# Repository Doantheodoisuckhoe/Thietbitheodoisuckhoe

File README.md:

# Thiết bị đeo tay giám sát sức khỏe người cao tuổi

Đồ án tốt nghiệp ngành Điện tử – Viễn thông.

Thiết bị đeo tay theo dõi nhịp tim, SpO2, nhiệt độ da, ECG 1 chuyển đạo và ước lượng huyết áp (PAT),
phát hiện té ngã, gửi cảnh báo tự động đến người thân qua app, web và SMS.

> Nguyên mẫu nghiên cứu, **không phải thiết bị y tế**, không dùng để chẩn đoán.

## Kiến trúc

```
Đồng hồ (XIAO nRF52840 Sense + module MAX30102 + AD8232 + MAX30205)
   │ BLE
   ▼
App Android (Flutter) ──Internet──► Server (FastAPI + PostgreSQL)
                                        │ khi vượt ngưỡng
                                        ▼
                         Người nhà, bác sĩ: push, SMS, web dashboard
```

## Cấu trúc thư mục

| Thư mục | Nội dung | Phụ trách |
|---|---|---|
| `firmware/` | Code Arduino/C cho XIAO nRF52840: đọc cảm biến, xử lý tín hiệu, BLE | SV1 |
| `algorithm/` | Thuật toán viết và kiểm thử bằng Python (nhịp tim, SpO2, Pan-Tompkins, PAT, té ngã) | SV2 |
| `app/` | App Flutter cho người đeo và người nhà; web dashboard (Flutter Web) | SV2 |
| `server/` | Backend FastAPI, cơ sở dữ liệu, bộ xử lý cảnh báo, gửi push/SMS | SV2 |
| `hardware/pcb_module/` | KiCad bản ghép module đang làm: sơ đồ, PCB 2 lớp, Gerber, BOM | SV1 |
| `hardware/pcb/` | KiCad bản chip rời 40 × 40 mm (lưu trữ, hướng phát triển) | SV1 |
| `hardware/enclosure/` | File thiết kế vỏ (Fusion 360, STL) | SV1 |
| `data/` | Dữ liệu đo thô (CSV) và kết quả kiểm chứng | Chung |
| `docs/` | Tài liệu, hình ảnh cho báo cáo | Chung |

## Phần cứng

| Khối | Linh kiện |
|---|---|
| Vi điều khiển + BLE + IMU | Seeed XIAO nRF52840 Sense |
| PPG (nhịp tim, SpO2) | Module MAX30102 (bản chip rời MAX30101 để hướng phát triển) |
| ECG 1 chuyển đạo | Module AD8232 |
| Nhiệt độ da | Module MAX30205 (CJMCU-30205) |
| Hiển thị, cảnh báo | Màn hình tròn 1,28" GC9A01, motor rung, nút SOS |
| Nguồn | Pin LiPo 603040 (có mạch bảo vệ), sạc qua chân pogo nam châm |

## Cài đặt môi trường

**Firmware (Arduino IDE)**
1. File → Preferences → Additional boards manager URLs:
   `https://files.seeedstudio.com/arduino/package_seeeduino_boards_index.json`
2. Boards Manager → cài **Seeed nRF52 Boards** (1.1.13) → chọn board **Seeed XIAO nRF52840 Sense**.
3. Library Manager → cài: SparkFun MAX3010x Pulse and Proximity Sensor Library, OneWire,
   DallasTemperature, Adafruit GC9A01A (chọn *Install all* để cài kèm Adafruit GFX, BusIO), Seeed Arduino LSM6DS3.
4. Mở `firmware/kiem_tra_thu_vien` và bấm Verify để kiểm tra. Phiên bản đã kiểm chứng và các lỗi
   thường gặp: [`firmware/README.md`](firmware/README.md).

**Vỏ thiết bị:** Onshape (gói Education, đăng ký bằng email sinh viên), xuất STL vào `hardware/enclosure/`.

**Thuật toán (Python 3.10+)**
```
pip install numpy scipy matplotlib wfdb pandas
```

## Mốc tiến độ

| Mốc | Hạn | Tiêu chí |
|---|---|---|
| M1 | 11/10/2026 | Đề cương được duyệt, linh kiện đã đặt |
| M2 | 01/11/2026 | Breadboard đo đủ chỉ số qua BLE; đã đặt mạch JLCPCB |
| M3 | 22/11/2026 | Thiết bị đeo tay chạy đầu-cuối ổn định 24 giờ |
| M4 | 06/12/2026 | Bản thảo báo cáo đầy đủ gửi GVHD |

## Tài liệu và công cụ của nhóm

| Ở đâu | Có gì |
|---|---|
| [`docs/nhat-ky.md`](docs/nhat-ky.md) | Nhật ký thực hiện và các quyết định theo ngày |
| [`docs/mua-sam/`](docs/mua-sam/) | Danh sách mua linh kiện, máy đo đối chứng, ngân sách |
| Trello: bảng *Đồ án – Thiết bị đeo tay giám sát sức khỏe* | Việc từng tuần, mốc; báo cáo tiến độ tự động tối Chủ Nhật |
| Google Drive: thư mục *Đồ án tốt nghiệp – Thiết bị đeo tay giám sát sức khỏe* | Datasheet, dữ liệu đo dài, báo cáo, ảnh/video, file phát hành mạch và vỏ, giấy tờ |

## Làm việc với Git trên máy

Thư mục làm việc trên máy SV1: `C:\DoAnTotNghiep` (bản clone của repo này).

1. Trước khi làm: mở Git Bash trong thư mục đó, chạy `git pull` để lấy thay đổi mới nhất.
2. Sau khi làm xong một việc nhỏ:
   ```
   git add .
   git commit -m "firmware: mô tả ngắn việc vừa làm"
   git push
   ```
3. Lần đầu `git push`, Windows sẽ mở cửa sổ đăng nhập GitHub — đăng nhập một lần là xong.

## Quy ước làm việc

- Mỗi người làm trên nhánh riêng (`sv1/...`, `sv2/...`), gộp vào `main` khi chạy được.
- Commit nhỏ, mô tả rõ bằng tiếng Việt, ví dụ: `firmware: đọc FIFO MAX30102 ở 100 Hz`.
- Không đẩy file lớn hơn 50 MB; dữ liệu đo dài lưu trên Drive, chỉ để mẫu nhỏ trong `data/`.

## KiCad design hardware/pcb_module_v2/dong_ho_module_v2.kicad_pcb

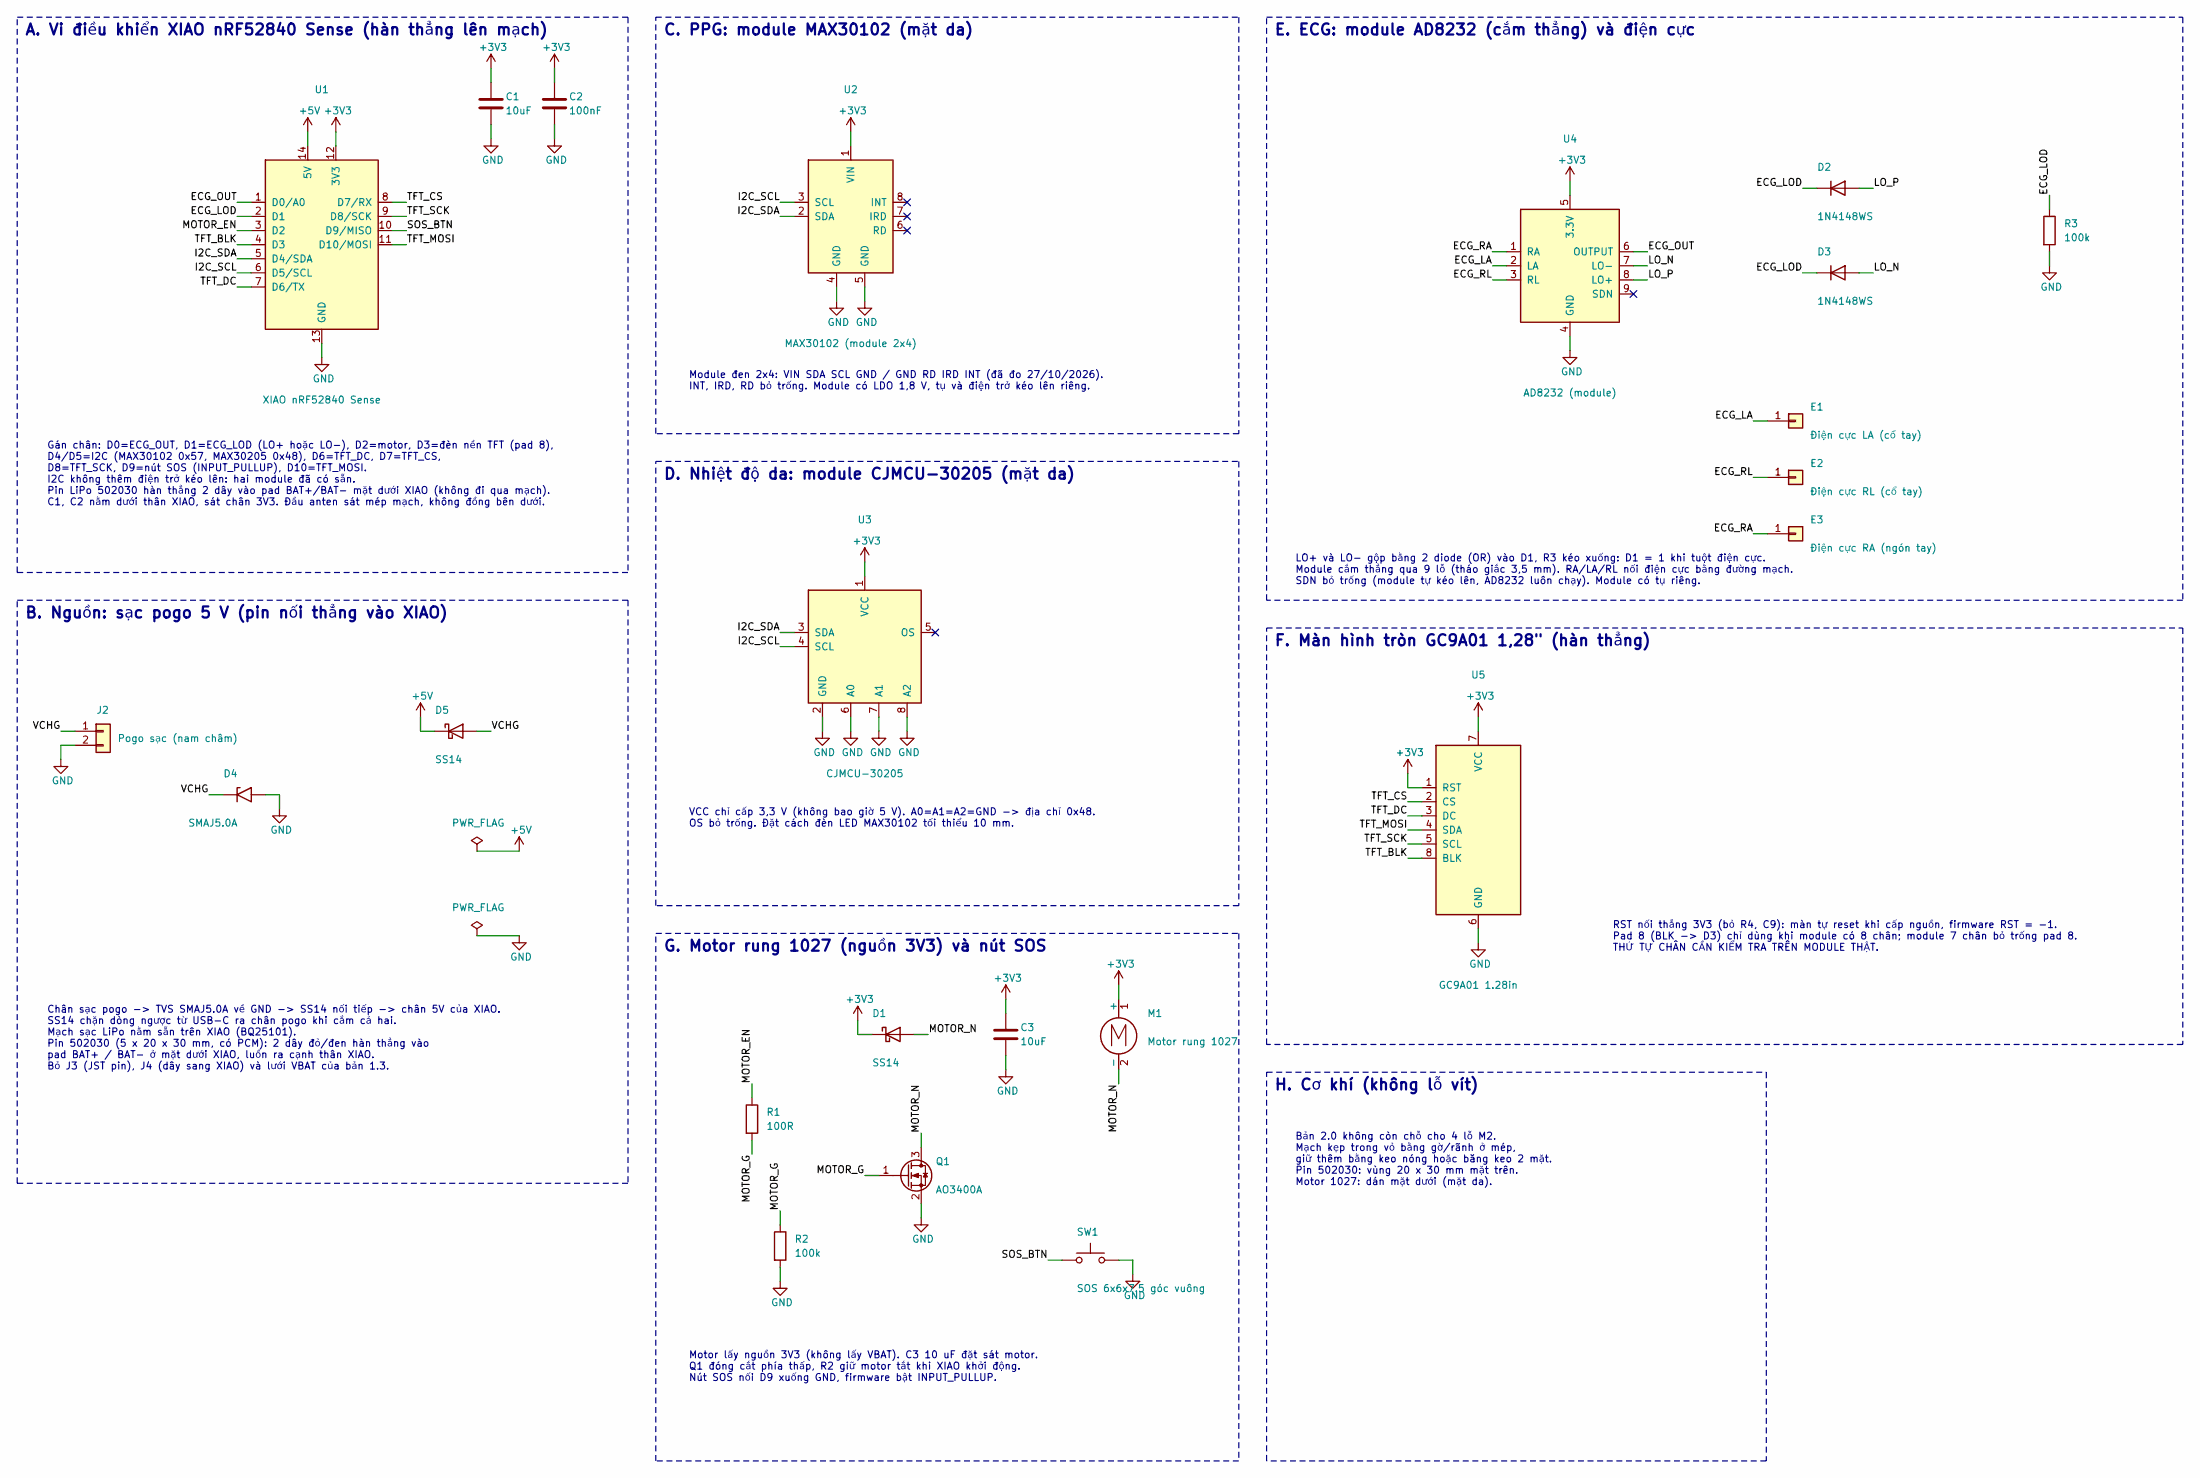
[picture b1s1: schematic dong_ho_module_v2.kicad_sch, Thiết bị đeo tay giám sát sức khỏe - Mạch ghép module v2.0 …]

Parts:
C1, C3: 10uF; C_0805_2012Metric
C2: 100nF; C_0805_2012Metric
D1, D5: SS14; D_SMA
D2, D3: 1N4148WS; D_SOD-323
D4: SMAJ5.0A; D_SMA
E1: Điện cực LA (cổ tay); DienCuc_ECG_9x16mm
E2: Điện cực RL (cổ tay); DienCuc_ECG_9x16mm
E3: Điện cực RA (ngón tay); DienCuc_RA_8x9.6mm
J2: Pogo sạc (nam châm); Pogo_2pad_P2.54_TAM
M1: Motor rung 1027; Motor_1027_2pad_P4.0_TAM
Q1: AO3400A; SOT-23
R1: 100R; R_0805_2012Metric
R2, R3: 100k; R_0805_2012Metric
SW1: SOS 6x6x7.5 góc vuông; SW_SOS_6x6_GocVuong_TAM
U1: XIAO nRF52840 Sense; XIAO_nRF52840_DeCam_2x7_P2.54_15.24mm
U2: MAX30102 (module 2x4); Module_MAX30102_2x4
U3: CJMCU-30205; Module_CJMCU-30205_1x8
U4: AD8232 (module); Module_AD8232_9chan
U5: GC9A01 1.28in; Display_GC9A01_8chan

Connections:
+3V3: C1.1, C2.1, C3.1, D1.1 (K), M1.1 (+), U1.12 (3V3), U2.1 (VIN), U3.1 (VCC), U4.5 (3.3V), U5.1 (RST), U5.7 (VCC)
+5V: D5.1 (K), U1.14 (5V)
/ECG_LA: E1.1, U4.2 (LA)
/ECG_LOD: D2.1 (K), D3.1 (K), R3.1, U1.2 (D1)
/ECG_OUT: U1.1 (D0/A0), U4.6 (OUTPUT)
/ECG_RA: E3.1, U4.1 (RA)
/ECG_RL: E2.1, U4.3 (RL)
/I2C_SCL: U1.6 (D5/SCL), U2.3 (SCL), U3.4 (SCL)
/I2C_SDA: U1.5 (D4/SDA), U2.2 (SDA), U3.3 (SDA)
/LO_N: D3.2 (A), U4.7 (LO-)
/LO_P: D2.2 (A), U4.8 (LO+)
/MOTOR_EN: R1.1, U1.3 (D2)
/MOTOR_G: Q1.1 (G), R1.2, R2.1
/MOTOR_N: D1.2 (A), M1.2 (-), Q1.3 (D)
/SOS_BTN: SW1.1, U1.10 (D9/MISO)
/TFT_BLK: U1.4 (D3), U5.8 (BLK)
/TFT_CS: U1.8 (D7/RX), U5.2 (CS)
/TFT_DC: U1.7 (D6/TX), U5.3 (DC)
/TFT_MOSI: U1.11 (D10/MOSI), U5.4 (SDA)
/TFT_SCK: U1.9 (D8/SCK), U5.5 (SCL)
/VCHG: D4.1 (A1), D5.2 (A), J2.1
GND: C1.2, C2.2, C3.2, D4.2 (A2), J2.2, Q1.2 (S), R2.2, R3.2, SW1.2, U1.13 (GND), U2.4 (GND), U2.5 (GND), U3.2 (GND), U3.6 (A0), U3.7 (A1), U3.8 (A2), U4.4 (GND), U5.6 (GND)

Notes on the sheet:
A. Vi điều khiển XIAO nRF52840 Sense (hàn thẳng lên mạch)
Gán chân: D0=ECG_OUT, D1=ECG_LOD (LO+ hoặc LO-), D2=motor, D3=đèn nền TFT (pad 8), D4/D5=I2C (MAX30102 0x57, MAX30205 0x48), D6=TFT_DC, D7=TFT_CS, D8=TFT_SCK, D9=nút SOS (INPUT_PULLUP), D10=TFT_MOSI. I2C không thêm điện trở kéo lên: hai module đã có sẵn. Pin LiPo 502030 hàn thẳng 2 dây vào pad BAT+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
B. Nguồn: sạc pogo 5 V (pin nối thẳng vào XIAO)
Chân sạc pogo -> TVS SMAJ5.0A về GND -> SS14 nối tiếp -> chân 5V của XIAO. SS14 chặn dòng ngược từ USB-C ra chân pogo khi cắm cả hai. Mạch sạc LiPo nằm sẵn trên XIAO (BQ25101). Pin 502030 (5 x 20 x 30 mm, có PCM): 2 dây đỏ/đen hàn thẳng vào pad BAT+ / BAT- ở mặt dưới XIAO, luồn ra cạnh thân XIAO. B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
C. PPG: module MAX30102 (mặt da)
Module đen 2x4: VIN SDA SCL GND / GND RD IRD INT (đã đo 27/10/2026). INT, IRD, RD bỏ trống. Module có LDO 1,8 V, tụ và điện trở kéo lên riêng.
D. Nhiệt độ da: module CJMCU-30205 (mặt da)
VCC chỉ cấp 3,3 V (không bao giờ 5 V). A0=A1=A2=GND -> địa chỉ 0x48. OS bỏ trống. Đặt cách đèn LED MAX30102 tối thiểu 10 mm.
E. ECG: module AD8232 (cắm thẳng) và điện cực
LO+ và LO- gộp bằng 2 diode (OR) vào D1, R3 kéo xuống: D1 = 1 khi tuột điện cực. Module cắm thẳng qua 9 lỗ (tháo giắc 3,5 mm). RA/LA/RL nối điện cực bằng đường mạch. SDN bỏ trống (module tự kéo lên, AD8232 luôn chạy). Module có tụ riêng.
F. Màn hình tròn GC9A01 1,28" (hàn thẳng)
RST nối thẳng 3V3 (bỏ R4, C9): màn tự reset khi cấp nguồn, firmware RST = -1. Pad 8 (BLK -> D3) chỉ dùng khi module có 8 chân; module 7 chân bỏ trống pad 8. THỨ TỰ CHÂN CẦN KIỂM TRA TRÊN MODULE THẬT.
G. Motor rung 1027 (nguồn 3V3) và nút SOS
Motor lấy nguồn 3V3 (không lấy VBAT). C3 10 uF đặt sát motor. Q1 đóng cắt phía thấp, R2 giữ motor tắt khi XIAO khởi động. Nút SOS nối D9 xuống GND, firmware bật INPUT_PULLUP.
H. Cơ khí (không lỗ vít)
Bản 2.0 không còn chỗ cho 4 lỗ M2. Mạch kẹp trong vỏ bằng gờ/rãnh ở mép, giữ thêm bằng keo nóng hoặc băng keo 2 mặt. Pin 502030: vùng 20 x 30 mm mặt trên. Motor 1027: dán mặt dưới (mặt da).

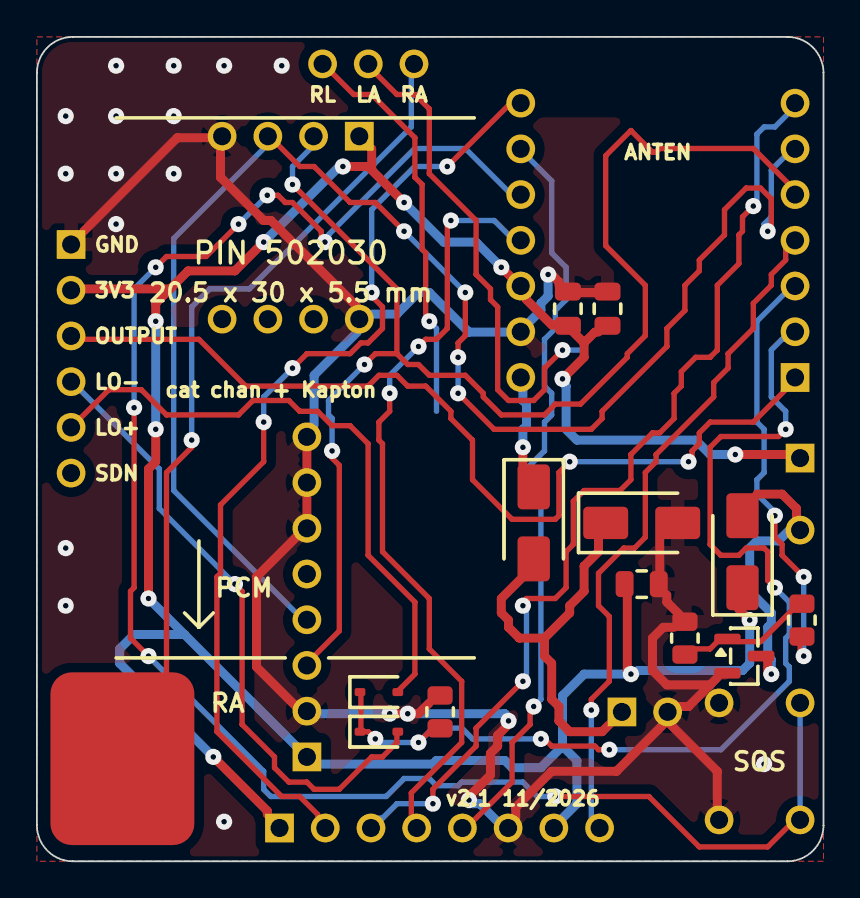
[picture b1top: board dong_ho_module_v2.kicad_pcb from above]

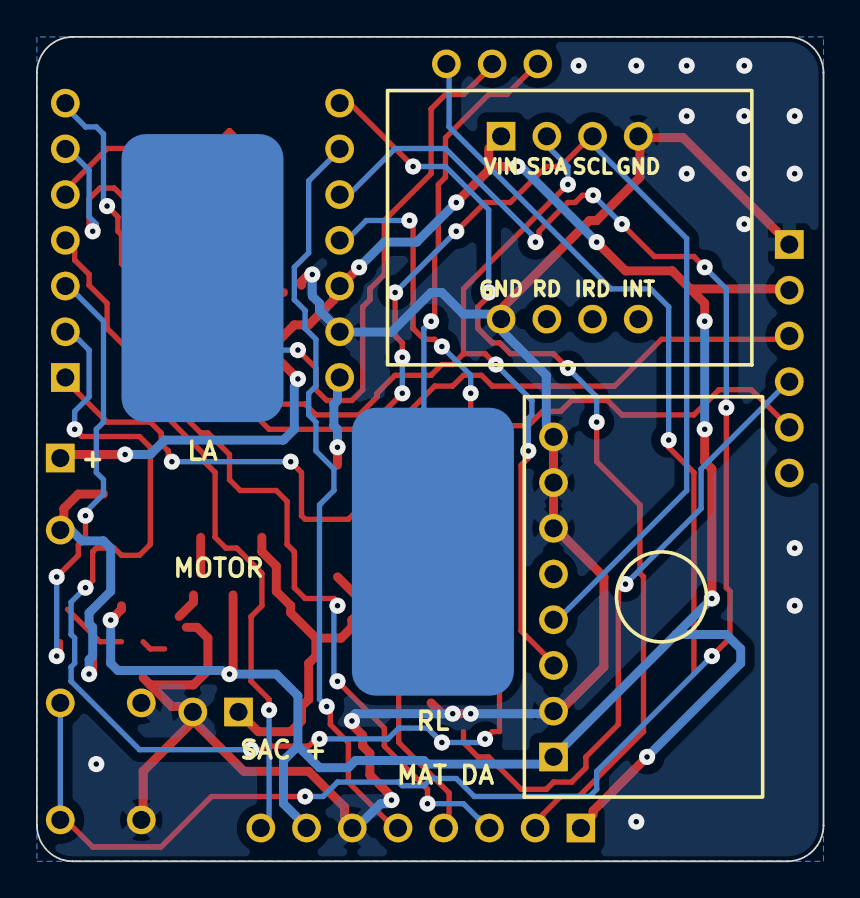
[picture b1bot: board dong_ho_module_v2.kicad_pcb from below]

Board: 2 copper layers, 43.7 x 45.8 mm, 23 parts (6 on the bottom side), 22 nets.

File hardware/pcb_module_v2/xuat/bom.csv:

"Reference","Value","Footprint","QUANTITY","Description"
"C1,C3","10uF","Capacitor_SMD:C_0805_2012Metric","2","Tụ gốm 0805 X5R/X7R, 10 V trở lên"
"C2","100nF","Capacitor_SMD:C_0805_2012Metric","1","Tụ gốm 0805 X5R/X7R, 10 V trở lên"
"D1,D5","SS14","Diode_SMD:D_SMA","2","Diode Schottky 40 V 1 A, SMA (D5: chặn dòng ngược về pogo; D1: dập xung ngược motor)"
"D2,D3","1N4148WS","Diode_SMD:D_SOD-323","2","Diode tín hiệu 75 V 150 mA, SOD-323 (cổng OR LO+ / LO-)"
"D4","SMAJ5.0A","Diode_SMD:D_SMA","1","TVS một chiều 5 V, 400 W, SMA (bảo vệ chân sạc)"
"J2","Pogo sạc (nam châm)","DoAnModule:Pogo_2pad_P2.54_TAM","1","Chân sạc pogo nam châm 2 chân hàn thẳng mặt dưới (TẠM, bước 2,54): 1 = +5V, 2 = GND"
"M1","Motor rung 1027","DoAnModule:Motor_1027_2pad_P4.0_TAM","1","Motor rung đồng xu 1027 (10 mm, 3 V), 2 dây hàn thẳng vào pad (TẠM bước 4,0 mm): 1 = +3V3, 2 = MOTOR_N"
"Q1","AO3400A","Package_TO_SOT_SMD:SOT-23","1","MOSFET kênh N 30 V 5,7 A, SOT-23 (đóng cắt motor)"
"R1","100R","Resistor_SMD:R_0805_2012Metric","1","Điện trở 0805, 1%"
"R2,R3","100k","Resistor_SMD:R_0805_2012Metric","2","Điện trở 0805, 1%"
"SW1","SOS 6x6x7.5 góc vuông","DoAnModule:SW_SOS_6x6_GocVuong_TAM","1","Nút nhấn 6x6x7,5 mm góc vuông hàn mép mạch (TẠM footprint 6,5 x 4,5 mm): 1 = D9, 2 = GND"
"U1","XIAO nRF52840 Sense","DoAnModule:XIAO_nRF52840_DeCam_2x7_P2.54_15.24mm","1","Seeed XIAO nRF52840 Sense hàn thẳng lên mạch bằng 2 hàng chân 1x7 (2,54 mm, hai hàng cách 15,24 mm)"
"U2","MAX30102 (module 2x4)","DoAnModule:Module_MAX30102_2x4","1","Module MAX30102 đen 2x4 chân (HW-605, I2C 0x57): 1 VIN, 2 SDA, 3 SCL, 4 GND, 5 GND, 6 RD, 7 IRD, 8 INT"
"U3","CJMCU-30205","DoAnModule:Module_CJMCU-30205_1x8","1","Module CJMCU-30205 (MAX30205, I2C 0x48 khi A0=A1=A2=GND), header 1x8: VCC GND SDA SCL OS A0 A1 A2. VCC chỉ 3,3 V"
"U4","AD8232 (module)","DoAnModule:Module_AD8232_9chan","1","Module AD8232 (ECG) cắm thẳng vào mạch qua 9 lỗ: 1 RA, 2 LA, 3 RL, 4 GND, 5 3V3, 6 OUTPUT, 7 LO-, 8 LO+, 9 SDN"
"U5","GC9A01 1.28in","DoAnModule:Display_GC9A01_8chan","1","Màn tròn 1,28"" GC9A01 (SPI) hàn thẳng vào mạch: 1 RST, 2 CS, 3 DC, 4 SDA, 5 SCL, 6 GND, 7 VCC, 8 BLK (pad 8 chỉ dùng với module 8 chân)"
